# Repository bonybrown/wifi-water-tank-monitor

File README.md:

# wifi-water-tank-monitor
ESP8266 based, solar powered, ultrasonic water tank level monitor

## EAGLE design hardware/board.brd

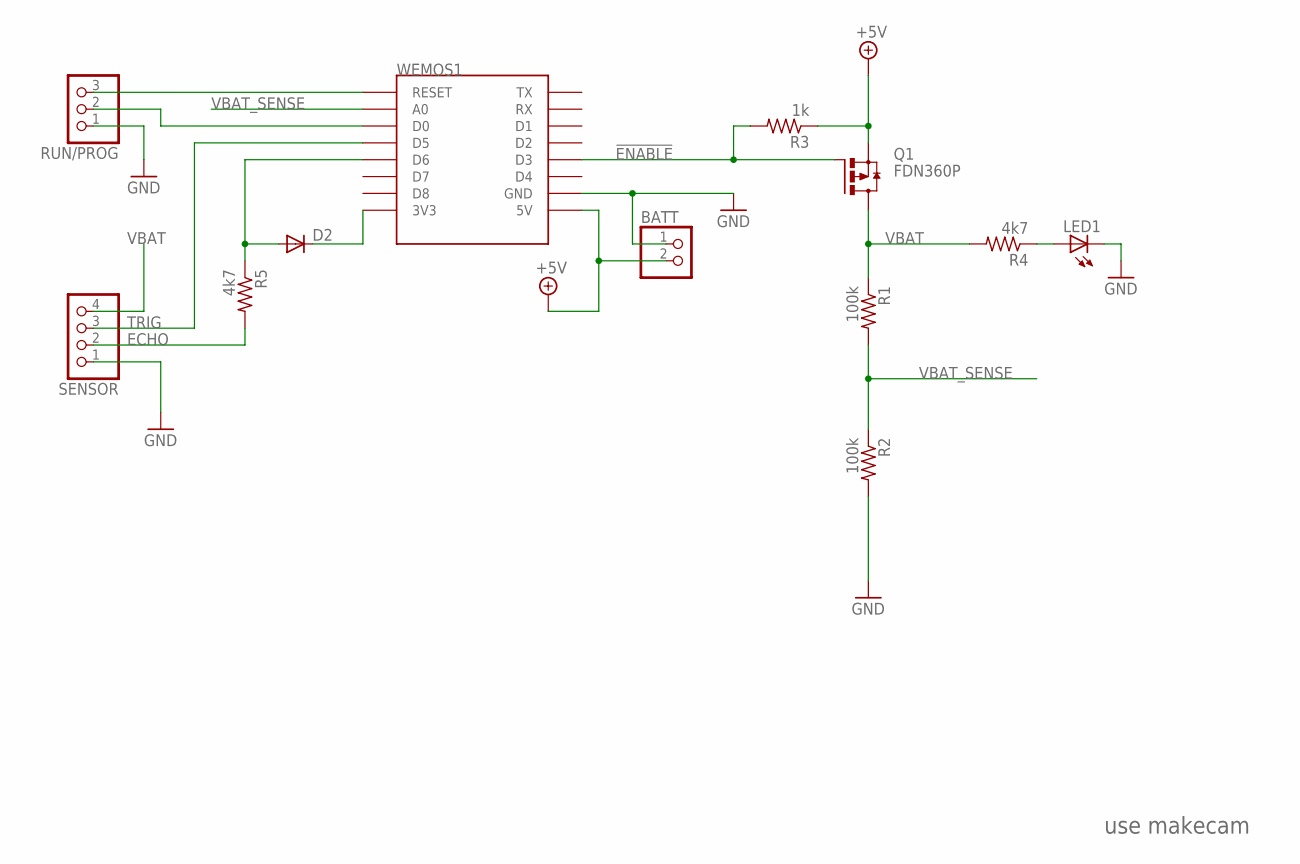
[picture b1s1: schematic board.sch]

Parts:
BATT: PINHD-1X2; 1X02
D2: DIODE-SOD323-W; SOD323-W
LED1: LEDSML1206; SML1206
Q1: FDN360P; SUPER-SOT3
R1, R2: 100k; R0805
R3: 1k; R0805
R4, R5: 4k7; R0805
REV1: REVISION
RUN/PROG: PINHD-1X3/90; 1X03/90
SENSOR: PINHD-1X4/90; 1X04/90
WEMOS1: WEMOS-D1-MINI

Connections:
!ENABLE: Q1.1 (G), R3.2, WEMOS1.D3
+5V: BATT.2, Q1.2 (S), R3.1, WEMOS1.5V
ECHO: R5.2, SENSOR.2
GND: BATT.1, LED1.C, R2.2, RUN/PROG.1, SENSOR.1, WEMOS1.GND
unnamed: RUN/PROG.3, WEMOS1.RESET
unnamed: RUN/PROG.2, WEMOS1.D0
unnamed: D2.C, WEMOS1.3V3
unnamed: LED1.A, R4.1
unnamed: D2.A, R5.1, WEMOS1.D6
TRIG: SENSOR.3, WEMOS1.D5
VBAT: Q1.3 (D), R1.1, R4.2, SENSOR.4
VBAT_SENSE: R1.2, R2.1, WEMOS1.A0

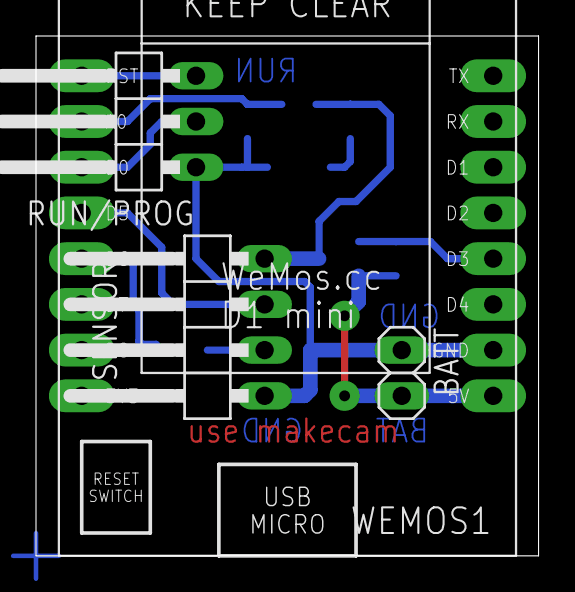
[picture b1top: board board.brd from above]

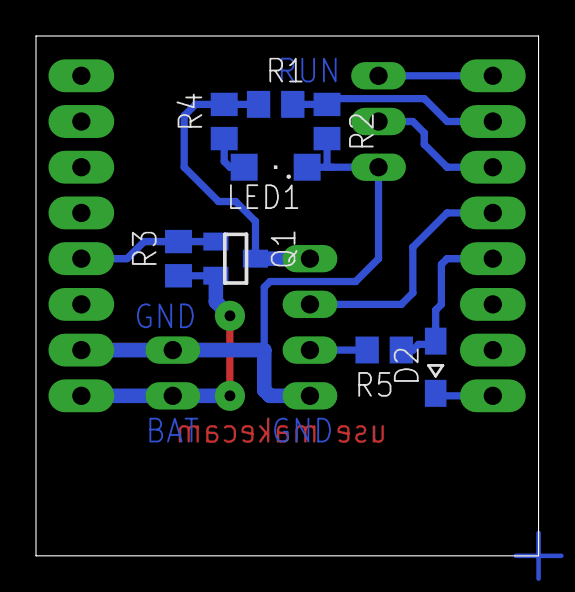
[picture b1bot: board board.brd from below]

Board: 2 copper layers, 27.9 x 28.9 mm, 13 parts (8 on the bottom side), 12 nets.

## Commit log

2019-04-27 Change dimensions to correct layer
2019-04-27 Added board revision for makecam
